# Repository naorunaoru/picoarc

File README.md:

# PicoARC

PicoARC is a device that appears to the host as a USB audio interface and passes through incoming audio as an S/PDIF-style stream to an ARC-compatible device. In simpler terms, this allows you to output audio from your computer to a soundbar or an ARC-capable receiver. It builds as USB Audio Class 1 by default for broad host compatibility; USB Audio Class 2 remains available as an opt-in target.

It also allows you to control the soundbar's volume. Somewhat. Because apparently supporting absolute volume control over CEC is not something that vendors are eager to implement.

Host volume and mute changes propagate to the soundbar in both USB modes. The
latest soundbar state is returned by subsequent USB control queries. UAC2 also
sends AudioControl change notifications; UAC1 has no notification endpoint, so
host volume controls generally remain stale after an on-device adjustment.
Host interfaces may ignore the UAC2 notifications as well.

Did I tell you it does HDMI-CEC too? Yes, it does, because it's required for ARC negotiation.

## Why?

There's no off-the-shelf way of doing this exact thing, surprisingly. The closest thing is using S/PDIF, which has limited bandwidth, sometimes incurs additional latency and definitely does not allow you to control the soundbar from the host.

## How does it work?

On the USB side, it acts as an audio interface, grabs the audio stream and passes it through.

On the HDMI side, it pretends to be a TV: responds to DDC queries with a plausible EDID, negotiates ARC with the connected audio system over CEC and drives the ARC line within the constraints defined by the HDMI 1.4 spec.

## Supported audio formats

- PCM at 32/44.1/48/88.2/96 kHz (higher sample rates are out of the question because RP2040 only has USB Full Speed)
- 16/20/24-bit

The optional UAC2 target additionally exposes separate IEC 61937 Dolby Digital
(AC-3) and DTS passthrough alternates. They are omitted from the default UAC1
target because host-driver support for Type III transport is inconsistent.

## Hardware

The PCB design lives under `hardware/`. The schematic source is written in
[Zener](https://docs.pcb.new/pages/spec), so `hardware/picoarc.zen` is the
schematic/netlist source of truth rather than a `.kicad_sch`; the KiCad layout
and JLCPCB production files are checked in alongside it.

See [hardware/README.md](hardware/README.md) for the hardware file map,
Zener/KiCad workflow, and the old hand-wired Pico prototype wiring.

## License

PicoARC uses a split license. Hardware design materials are licensed under
`CERN-OHL-W-2.0`, and firmware plus general project documentation are licensed
under `MIT`. See [LICENSE](LICENSE) for the exact scope and full license text
locations.

## Build requirements

- Git
- CMake and Ninja
- Arm GNU toolchain
- `picotool`

The Pico SDK and TinyUSB sources are pinned as git submodules under
`firmware/third_party`; builds do not use SDK copies installed on the host.
PicoARC uses Pico SDK 2.2.0 and upstream TinyUSB 0.21.0.

## Build

From this directory:

```sh
git submodule update --init --recursive
make build
```

This configures and builds both firmware variants:

```text
firmware/build-release/picoarc-release.uf2
firmware/build-debug/picoarc-debug.uf2
```

Those are UAC1 builds. To build the opt-in UAC2 target instead:

```sh
make build-uac2
```

Its artifacts use separate build directories and names so CMake and host USB
caches cannot mix the two personalities:

```text
firmware/build-release-uac2/picoarc-release-uac2.uf2
firmware/build-debug-uac2/picoarc-debug-uac2.uf2
```

UAC1 is the recommended full-speed target and is the mode tested for Windows
compatibility. Treat UAC2 as experimental on full-speed hosts; it is retained
for IEC 61937 and uses an adaptive OUT endpoint without explicit feedback. The
firmware follows the host's delivery rate by servoing the S/PDIF PIO clock from
the receive-buffer level.

The equivalent helper option is `--usb-audio-class uac2` (or `--uac uac2`),
for example `./picoarc build release --uac uac2`. Direct CMake builds can set
`-DPICOARC_USB_AUDIO_CLASS=uac2`; omitting the option selects UAC1.

By default PicoARC keeps sending silence for five minutes after the host closes
its audio stream, then stops the ARC/S/PDIF carrier so the soundbar can go to
standby. This can prevent short notification sounds from being swallowed while
the soundbar wakes during gaps between playback. To change the timeout, edit
`firmware/src/picoarc_config.h` before building:

```c
#define PICOARC_IDLE_AUDIO_TIMEOUT_SECONDS 300
```

Use `0` to stop immediately, positive seconds for a timeout, or `-1` to keep
sending silence forever. Reopening the stream cancels the countdown; the next
close starts a fresh countdown. Silent audio within an open stream and temporary
buffer refills do not start it. With a finite timeout, the carrier stays off at
boot until a stream opens; `-1` sends silence from boot.

The release variant is audio-only with logging compiled out. It waits for an
HDMI ARC device, completes ARC/SAD capability discovery, asks the soundbar for
its OSD name, and then enumerates as USB audio using that name when the soundbar
provides one. USB sample rates are limited to the connected soundbar's reported
capabilities. UAC1 lists rates separately for each PCM bit depth; UAC2 reports
the available rates on its shared clock and validates the selected format when
starting a stream. Unsupported bit depths and codecs are omitted. UAC2 rejects
unsupported rate requests; UAC1 rounds them to a supported rate and reports the
selected value through GET_CUR. When SAD discovery is unavailable, the existing
fallback remains 16-bit PCM at 48 kHz.

Capabilities are frozen for each USB connection and refreshed by re-enumerating
when they change. The initial rate is 48 kHz if supported, otherwise the nearest
supported rate. The debug variant initially exposes its serial log and reset
interface with no streaming alternates, then briefly reconnects USB when audio
capabilities become available or change.

## Host sanitizer tests

The host tests require CMake, Ninja, and a native Clang or GCC installation
with AddressSanitizer and UndefinedBehaviorSanitizer runtimes. They do not need
the Pico SDK or Arm compiler, but the TinyUSB submodule must be initialized. Run them with the
default C compiler or select one before the first configure:

```sh
make test-sanitizers
CC=clang make test-sanitizers
```

The compiler selection is cached in `firmware/build-host-sanitizers`; remove
that generated directory before switching compilers. The tests compile the
same USB audio sample decoder used by the firmware and cover the supported
16-, 20-, and 24-bit subslots, including IEC 61937 words, unaligned byte input,
buffer bounds, and the maximum audio-task batch. They also compile the real USB
descriptors and control callbacks for both audio classes and debug layouts,
checking sample-rate negotiation, sink changes, fallback capabilities, and
unsupported format/rate requests.

Run the idle timeout checks for both USB audio classes with a simulated clock:

```sh
python3 firmware/tests/test_idle_audio.py
```

The RP2040 firmware remains on its normal embedded build path and is not
instrumented. Host tests cannot validate DMA and PIO timing, multicore races,
interrupt behavior, or flash-blackout behavior on the device.

## Flash

Connect the Pico over USB, then run:

```sh
make flash
```

The helper script builds the release firmware first, then uses `picotool` to
load and run the UF2. If the Pico is not detected, hold BOOTSEL while plugging
it in and run the command again.

To flash the optional UAC2 release build, use `make flash-uac2`.

## Monitor

To open the USB serial log:

```sh
make monitor
```

To build, flash, and then open the monitor in one step:

```sh
make run
```

This flashes the debug variant, because the release variant does not expose a
USB serial log.

`make run-uac2` does the same with the optional UAC2 debug build.

Press `Ctrl-]` to close the monitor.

## Inspect silent audio

For a connected adapter that stops producing sound while volume controls still
work, an optional release build exposes read-only USB audio diagnostics while
keeping the same audio interfaces and descriptors:

```sh
cmake -S firmware -B firmware/build-diagnostics-uac2 -G Ninja \
  -DPICOARC_VARIANT=release -DPICOARC_USB_AUDIO_CLASS=uac2 \
  -DPICOARC_USB_DIAGNOSTICS=ON
cmake --build firmware/build-diagnostics-uac2
```

Flash `firmware/build-diagnostics-uac2/picoarc-release-uac2-diagnostics.uf2`
using BOOTSEL, then capture during playback or a failure before reconnecting USB:

```sh
python3 tools/audio_probe.py --seconds 30 > audio-diagnostics.jsonl
```

The probe requires libusb and reports audio counters, ARC gating, DMA progress,
output hardware state, and reset cause without clearing counters or claiming
interfaces.
During a bounded capture it waits for the adapter to return after a KVM switch;
an uptime reset means the board rebooted, while `watchdog_timeout` and
`watchdog_forced` distinguish watchdog resets from hardware resets.
Reset-cause flags require diagnostic protocol version 2; output registers,
nonzero encoded-frame counts, and encoder/buffer hashes require version 3,
and unavailable fields are omitted for older firmware.
Growing USB/frame counters with a stopped DMA block counter indicate a stuck
output core; a closed format gate points to ARC/capability state, while growing
DMA blocks with admitted nonzero audio require checking the carrier and receiver.
Diagnostics are disabled by default and provide evidence for debugging rather
than changing recovery behavior.

Protocol 3 diagnostics also provide an explicit software BOOTSEL command;
ordinary captures remain read-only, and rebooting requires the board's USB
serial number:

```sh
python3 tools/audio_probe.py --bootsel --serial YOUR_BOARD_SERIAL
```

Protocol 4 can also copy the encoded 192-frame buffer currently being consumed
by DMA, without pausing playback:

```sh
python3 tools/audio_probe.py --spdif-block --serial YOUR_BOARD_SERIAL
```

The snapshot includes the encoded words, current PIO instruction and pin-pad
configuration. The host decoder checks preambles, BMC transitions, parity and
sample validity, and reports PCM peak/RMS levels and channel-status bytes.
Copies that cross a DMA buffer handoff are marked unstable and must be retried.
This checks the data supplied to PIO; it does not measure the HDMI waveform or
confirm that the soundbar has locked onto it. Ordinary captures omit this larger
snapshot.

Protocol 5 adds two explicit recovery commands, both requiring the matching
USB serial number:

```sh
python3 tools/audio_probe.py --recover output --serial YOUR_BOARD_SERIAL
python3 tools/audio_probe.py --recover usb --serial YOUR_BOARD_SERIAL
```

Capture the failed stream first, then try one recovery at a time. `output`
asks core 1 to restart its S/PDIF state machine and DMA without restarting USB
or ARC negotiation. `usb` reconnects the USB audio device without rebooting the
adapter or reinitializing the S/PDIF state machine. Both briefly interrupt
playback. Read-only captures report output request/completion counters and USB
reconnect requests; an accepted command is not proof that sound has returned.
These commands are diagnostic experiments, not automatic recovery policies.

Protocol 6 adds read-only HPD/DDC controller state and cached soundbar volume
and mute reports, plus an explicit HDMI recovery command:

```sh
python3 tools/audio_probe.py --recover hdmi --serial YOUR_BOARD_SERIAL
```

This reconnects USB, resets the EDID responder and ARC session, and pulses HPD
while retaining processor uptime and the S/PDIF transmitter configuration.
It briefly interrupts playback and reports the request in subsequent captures.
Test it during a captured silent failure to determine whether that boundary
restores sound; an accepted request alone does not establish recovery.

Protocol 8 retains the last 128 observed USB/ARC state changes, streaming-alt
requests, parsed CEC frames and CEC transmit results in memory, with timestamps
and sequence numbers. Capture this history before a reset; reads preserve it,
while a processor restart clears it:

```sh
python3 tools/audio_probe.py --trace --spdif-block --serial YOUR_BOARD_SERIAL
```

The following manual tests separate parts of the combined HDMI recovery:

| Command | Direct action |
| --- | --- |
| `--recover ddc` | Reset only the EDID I2C controller, FIFOs and byte parser |
| `--recover cec-rx` | Reset only the CEC receiver and parser |
| `--recover cec` | Resend the existing system-audio and ARC-initiation requests |
| `--recover hpd` | Pulse HPD low for 200 ms, retaining cached ARC and EDID state |

Each command requires `--serial`; none explicitly reconnects USB or restarts
the audio transmitter, although soundbar replies can trigger normal ARC/USB
state changes. Try one command at a time during a captured silent failure and
check audibility and the trace before proceeding; these diagnostics introduce
no automatic recovery or idle refresh.

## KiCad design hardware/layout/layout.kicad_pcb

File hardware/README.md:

# PicoARC Hardware

The PicoARC PCB design lives in this directory. This branch contains
[completed USB-powered DDC routing](experiments/usb-powered-ddc.md) for using
the board with separate monitor-flashing firmware. Layout checks pass;
electrical bring-up remains outstanding. The circuit is
authored with the [Zener](https://docs.pcb.new/pages/spec) toolchain from
[Diode](https://github.com/diodeinc/pcb), and the physical board layout is kept
as a generated/synced [KiCad](https://kicad.org/) project.

## Source of Truth

Zener is a Starlark-based hardware description language for PCB schematics. The
`pcb` CLI evaluates the `.zen` design, manages dependencies from `pcb.toml`,
assigns reference designators, validates the netlist, and generates/syncs KiCad
layout files.

In this repo, the `.zen` files are the schematic source of truth. There is no
separate `.kicad_sch` to edit:

- `picoarc.zen` is the top-level board schematic/netlist.
- `modules/` contains reusable schematic subcircuits for USB-C, power, HDMI
  ARC, and debug/status hardware.
- `components/` contains local RP2040 and flash component definitions.
- `footprints/` contains local symbols, footprints, and 3D models not taken
  directly from the upstream KiCad libraries.

Edit the Zen module tree when changing the circuit, then regenerate/sync the
KiCad layout from that source.

## Debug Probe Access

`TP_SWD` is a compact row of three 1.0 x 2.0 mm edge test pads on 1.5 mm pitch.
Connect it to Raspberry Pi Debug Probe using pogo pins or soldered leads. Its
target-side pinout is:

- pin 1: SWCLK / SC
- pin 2: GND
- pin 3: SWDIO / SD

The SWCLK and SWDIO pads currently connect directly to the RP2040. Target-side
100 ohm series termination is intentionally omitted while the board layout is
in flux and should be reconsidered before fabrication. The center ground pad
and the board's other solderable ground test pads use thermal-relief zone
connections to make hand soldering practical.

## Layout and Production Files

- `pcb.toml` is the Zener workspace/board manifest. It pins the board entry
  point, repository metadata, `pcb-version`, and KiCad library dependencies.
- `layout/layout.kicad_pro` is the KiCad project to open for board review.
- `layout/layout.kicad_pcb` is the checked-in PCB layout.
- `layout/layout.kicad_dru` contains KiCad design rules.
- `layout/jlcpcb/gerber/` contains the plotted Gerber/drill outputs.
- `layout/jlcpcb/production_files/` contains the current JLCPCB upload bundle:
  `GERBER-layout.zip`, `BOM-layout.csv`, and `CPL-layout.csv`.
- `jlcpcb-lcsc.csv` records JLCPCB/LCSC sourcing data used by the board.

## Zener/KiCad Workflow

Install the `pcb` shim using the
[upstream instructions](https://docs.pcb.new/pages/quickstart). The shim selects
the `pcbc` toolchain lane requested by `pcb.toml`; this repo currently requests
the `0.3` lane.

After changing the Zen schematic, run from this directory:

```sh
pcb sync
pcb build picoarc.zen
pcb layout picoarc.zen
```

`pcb sync` reconciles imports and dependency manifests. `pcb build` evaluates
and validates the Zener design. `pcb layout` regenerates/syncs the KiCad layout
project from the Zen netlist.

After that, open `layout/layout.kicad_pro` in KiCad for placement/routing
review, DRC, and fabrication exports. KiCad remains the tool for inspecting and
finishing the physical layout; Zener remains the tool for changing the circuit.

## Prototype Wiring

If you want to reproduce the old hand-wired Pico dev-board prototype instead,
the minimal wiring is:

- Pi Pico dev board
- HDMI breakout
- Few passives you probably have laying around
- 3.3 V <-> 5 V I2C level shifter for HDMI DDC/EDID (or not, if you're brave)

```text
Net CEC_BUS
  Pico 3V3 (pin 36)  -- R1 (27 kOhm) -- node CEC_BUS
  Pico GP3 (pin 5)   -- R2 (220 Ohm) -- node CEC_BUS
  node CEC_BUS                         -- HDMI pin 13

Net ARC_TX
  Pico GP2 (pin 4)   -- R3 (330 Ohm) -- node ATT_A
  node ATT_A         -- R4 (56 Ohm)  -- Pico GND
  node ATT_A         -- C1 (10 nF)   -- HDMI pin 14

Net HDMI_5V_FROM_SOUNDBAR
  HDMI pin 18        -- R5 (1 kOhm)   -- HDMI pin 19
  HDMI pin 18        -- R6 (68 kOhm)  -- node HDMI_5V_SENSE
  node HDMI_5V_SENSE                   -- Pico GP4 (pin 6)
  node HDMI_5V_SENSE -- R7 (100 kOhm) -- Pico GND

Net DDC_EDID
  HDMI pin 15 (SCL)  -- level shifter -- Pico GP7 (pin 10)
  HDMI pin 16 (SDA)  -- level shifter -- Pico GP6 (pin 9)

Net GND
  Pico GND (pin 38)                    -- HDMI pin 17
```

Note about DDC_EDID: while omitting a level shifter works as a bench-only direct
GPIO bodge, keep in mind that HDMI DDC is a 5 V bus and RP2040 IO is not exactly
5 V tolerant.

## License

The PicoARC hardware design materials in this directory are licensed under the
CERN Open Hardware Licence Version 2 - Weakly Reciprocal (`CERN-OHL-W-2.0`).
See [../LICENSE](../LICENSE) for the repository license notice and full license
text locations.

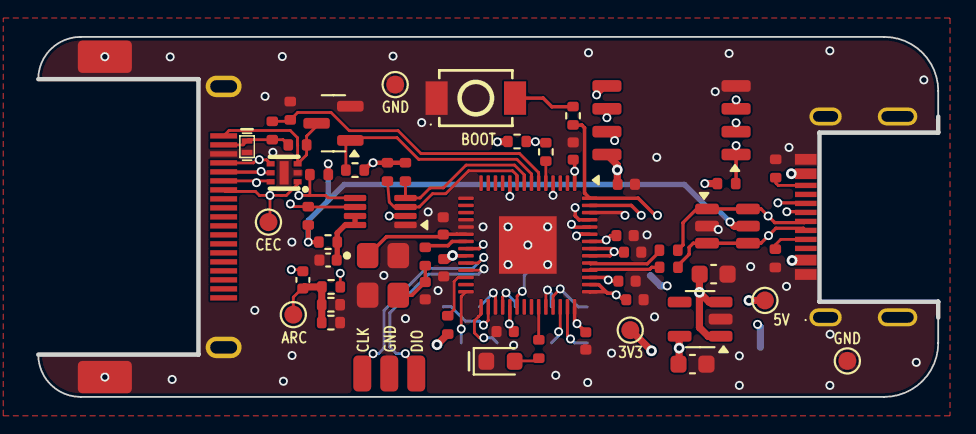
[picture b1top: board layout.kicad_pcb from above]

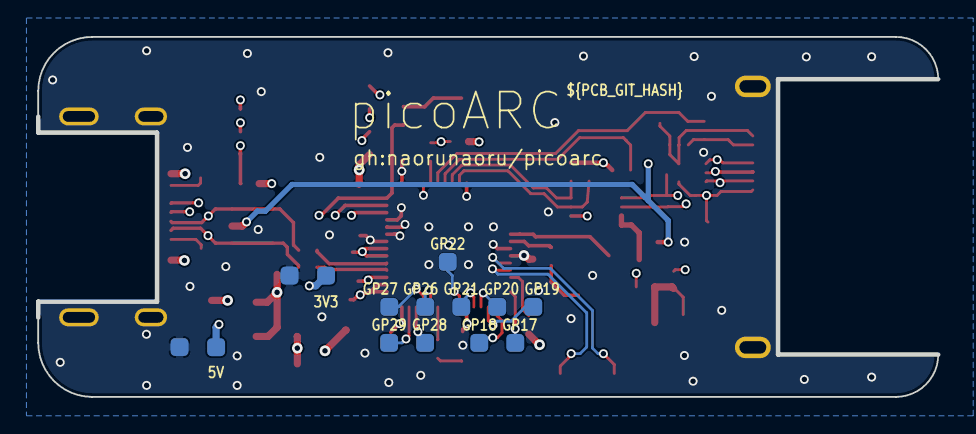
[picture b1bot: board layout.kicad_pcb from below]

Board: 4 copper layers, 50.0 x 19.8 mm, 72 parts (14 on the bottom side), 49 nets.

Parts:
C1: CL05B103KB5NNNC; C_0402_1005Metric
C2: 0402CG101J500NT; C_0402_1005Metric
C3, C4: CL10A106MA8NRNC; C_0603_1608Metric
C5, C8, C9, C10, C11, C12, C13: CL05B104KB54PNC; C_0402_1005Metric
C6, C7: CL05A105KA5NQNC; C_0402_1005Metric
C14, C15: 0402CG330J500NT; C_0402_1005Metric
D1: KT-0603R; LED_0603_1608Metric
D2: D5V0M5B6LP16-7; DFN1616-6_L1.6-W1.6-P0.50-BL-EP
D3: H7VH10U; SOD-882_L1.0-W0.6-BI
J1: HC-HDMI0019T-3; HDMI-SMD_HC-HDMI0019T-3_PicoARC_R6
J2: GT-USB-7014G; USB-C-SMD_GT-USB-7014D
Q1: 2N7002; SOT-23
R1: 0402WGF2202TCE; R_0402_1005Metric
R2: 0402WGF2200TCE; R_0402_1005Metric
R3: 0402WGF3300TCE; R_0402_1005Metric
R4, R5, R16, R23: 0402WGF1001TCE; R_0402_1005Metric
R6, R7, R13: 0402WGF1003TCE; R_0402_1005Metric
R8, R9, R10, R11: 0402WGF2201TCE; R_0402_1005Metric
R12: 0402WGF2003TCE; R_0402_1005Metric
R14: 0402WGF1000TCE; R_0402_1005Metric
R15: 0402WGF1200TCE; R_0402_1005Metric
R17, R18: 0402WGF5101TCE; R_0402_1005Metric
R19, R20: 0402WGF1002TCE; R_0402_1005Metric
R21, R22: 0402WGF330JTCE; R_0402_1005Metric
SW1: TS-1088-AR02016; SW-SMD_L3.9-W3.0-P4.45
TP1, TP2, TP3, TP4, TP5, TP6, TP7, TP8, TP9, TP10, TP11, TP12, TP13, TP14: ?; TestPad_1.0x1.0mm_RoundRect
TP15: ?; SWD_EdgePads_1x03_P1.50mm
TP16, TP17, TP18, TP19, TP20, TP21: ?; TestPoint_Pad_D1.0mm
U1: PCA9306DCUR; VSSOP-8_2.3x2mm_P0.5mm
U2: AP2112K-3.3TRG1; SOT-23-5
U3: USBLC6-2SC6; SOT-23-6
U4: W25Q16JVSSIQ; SOIC-8_5.3x5.3mm_P1.27mm
U5: RP2040; QFN-56-1EP_7x7mm_P0.4mm_EP3.2x3.2mm
Y1: X322512MSB4SI; Crystal_SMD_3225-4Pin_3.2x2.5mm

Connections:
ARC_TX: R3.1, U5.4
ATT_A: C1.1, R3.2, R14.1, R15.1, TP18.1
BOOTSEL_SW: R16.2, SW1.1
CEC_BUS: R2.1, U5.5
CEC_NODE: D2.1, J1.13, R1.2, R2.2, TP19.1
DBG.STATUS_LED_A: D1.2, R4.2
DDC_SCL: R8.1, U1.3, U5.9
DDC_SCL_5V: D2.5, J1.15, R10.1, U1.6
DDC_SDA: R9.1, U1.4, U5.8
DDC_SDA_5V: D2.4, J1.16, R11.1, U1.5
GND: C2.2, C3.2, C4.2, C5.2, C6.2, C7.2, C8.2, C9.2, C10.2, C11.2, C12.2, C13.2, C14.2, C15.2, D1.1, D2.2, D2.7, D3.2, J1.17, J1.SH, J2.A1, J2.A12, J2.B1, J2.B12, J2.S1, Q1.2, R7.2, R14.2, R15.2, R17.2, R18.2, SW1.2, TP3.1, TP4.1, TP15.2, TP20.1, TP21.1, U1.1, U2.2, U3.2, U4.4, U5.19, U5.57, Y1.2, Y1.4
GP17: TP5.1, U5.28
GP18: TP6.1, U5.29
GP19: TP7.1, U5.30
GP20: TP8.1, U5.31
GP21: TP9.1, U5.32
GP22: TP10.1, U5.34
GP26: TP11.1, U5.38
GP27: TP12.1, U5.39
GP28: TP13.1, U5.40
GP29: TP14.1, U5.41
HDMI._ARC14: C1.2, D2.6, J1.14
HDMI._HDMI_5V: D3.1, J1.18, R5.1, R6.1
HDMI._HPD: D2.3, J1.19, Q1.3, R5.2
HDMI._VREF2_EN: C2.1, R12.2, U1.7, U1.8
HDMI_5V_SENSE: R6.2, R7.1, U5.6
HPD_GATE: Q1.1, R13.1, U5.7
QSPI_CLK: U4.6, U5.52
QSPI_CS: R16.1, R19.1, U4.1, U5.56
QSPI_IO0: U4.5, U5.53
QSPI_IO1: U4.2, U5.55
QSPI_IO2: U4.3, U5.54
QSPI_IO3: U4.7, U5.51
RUN: R20.1, U5.26
STATUS_LED: R4.1, U5.37
SWD_SWCLK: TP15.1, U5.24
SWD_SWDIO: TP15.3, U5.25
USBC.CC1: J2.A5, R17.1
USBC.CC2: J2.B5, R18.1
USB_D_N: J2.A7, J2.B7, R21.2, U3.3, U3.4
USB_D_P: J2.A6, J2.B6, R22.2, U3.1, U3.6
U_MCU.RP_USB_D_N: R21.1, U5.46
U_MCU.RP_USB_D_P: R22.1, U5.47
U_MCU._R_OSC: C15.1, R23.1, Y1.3
U_MCU.oscpair_XIN: C14.1, U5.20, Y1.1
U_MCU.oscpair_XOUT: R23.2, U5.21
VDD_1V1: C6.1, C8.1, C9.1, U5.23, U5.45, U5.50
VDD_3V3: C4.1, C5.1, C7.1, C10.1, C11.1, C12.1, C13.1, R1.1, R8.2, R9.2, R13.2, R19.2, R20.2, TP1.1, TP16.1, U1.2, U2.5, U4.8, U5.1, U5.10, U5.22, U5.33, U5.42, U5.43, U5.44, U5.48, U5.49
VDD_5V: C3.1, J2.A4, J2.A9, J2.B4, J2.B9, R10.2, R11.2, R12.1, TP2.1, TP17.1, U2.1, U2.3, U3.5

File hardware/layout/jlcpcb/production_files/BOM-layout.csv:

Comment,Designator,Footprint,LCSC,Quantity
D5V0M5B6LP16-7,D2,DFN1616-6_L1.6-W1.6-P0.50-BL-EP,C445551,1
H7VH10U,D3,SOD-882_L1.0-W0.6-BI,C7420372,1
TS-1088-AR02016,SW1,SW-SMD_L3.9-W3.0-P4.45,C720477,1
0402WGF3300TCE,R3,R_0402_1005Metric,,1
0402WGF1001TCE,R5,R_0402_1005Metric,,1
RP2040,U5,QFN-56-1EP_7x7mm_P0.4mm_EP3.2x3.2mm,,1
0402WGF1200TCE,R15,R_0402_1005Metric,,1
0402WGF2202TCE,R1,R_0402_1005Metric,,1
CL05B104KB54PNC,C13,C_0402_1005Metric,,1
0402WGF2201TCE,R10,R_0402_1005Metric,,1
0402WGF1001TCE,R16,R_0402_1005Metric,,1
CL05B104KB54PNC,C8,C_0402_1005Metric,,1
CL05A105KA5NQNC,C7,C_0402_1005Metric,,1
0402WGF1003TCE,R6,R_0402_1005Metric,,1
CL05B104KB54PNC,C9,C_0402_1005Metric,,1
CL05B104KB54PNC,C11,C_0402_1005Metric,,1
0402WGF1002TCE,R20,R_0402_1005Metric,,1
0402WGF1000TCE,R14,R_0402_1005Metric,,1
0402WGF1001TCE,R23,R_0402_1005Metric,,1
CL05B104KB54PNC,C12,C_0402_1005Metric,,1
0402WGF2201TCE,R9,R_0402_1005Metric,,1
0402CG330J500NT,C15,C_0402_1005Metric,,1
0402CG101J500NT,C2,C_0402_1005Metric,,1
0402CG330J500NT,C14,C_0402_1005Metric,,1
CL05B104KB54PNC,C5,C_0402_1005Metric,,1
CL05B104KB54PNC,C10,C_0402_1005Metric,,1
0402WGF1003TCE,R7,R_0402_1005Metric,,1
0402WGF1002TCE,R19,R_0402_1005Metric,,1
0402WGF1001TCE,R4,R_0402_1005Metric,,1
CL10A106MA8NRNC,C3,C_0603_1608Metric,,1
CL05A105KA5NQNC,C6,C_0402_1005Metric,,1
CL05B103KB5NNNC,C1,C_0402_1005Metric,,1
AP2112K-3.3TRG1,U2,SOT-23-5,,1
CL10A106MA8NRNC,C4,C_0603_1608Metric,,1
2N7002,Q1,SOT-23,,1
208658-1001,J1,HDMI_A_Molex_208658-1001_Horizontal,,1
0402WGF5101TCE,R18,R_0402_1005Metric,,1
USBLC6-2SC6,U3,SOT-23-6,,1
X322512MSB4SI,Y1,Crystal_SMD_3225-4Pin_3.2x2.5mm,,1
0402WGF2200TCE,R2,R_0402_1005Metric,,1
W25Q16JVSSIQ,U4,SOIC-8_5.3x5.3mm_P1.27mm,,1
0402WGF330JTCE,R22,R_0402_1005Metric,,1
0402WGF2003TCE,R12,R_0402_1005Metric,,1
USB4105-GF-A-060,J2,USB_C_Receptacle_GCT_USB4105-xx-A_16P_TopMnt_Horizontal,,1
0402WGF1003TCE,R13,R_0402_1005Metric,,1
0402WGF2201TCE,R11,R_0402_1005Metric,,1
0402WGF2201TCE,R8,R_0402_1005Metric,,1
0402WGF5101TCE,R17,R_0402_1005Metric,,1
KT-0603R,D1,LED_0603_1608Metric,,1
PCA9306DCTR,U1,VSSOP-8_2.3x2mm_P0.5mm,,1
0402WGF330JTCE,R21,R_0402_1005Metric,,1

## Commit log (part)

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2026-05-18 initial firmware, works as 16bit 48khz sink
2026-05-18 feat: CEC in PIO
2026-05-19 fix: rm player persona experiments
2026-05-19 feat(cec): TX via PIO+DMA with yield-aware wait
    Move CEC transmission and the per-byte ACK slot onto a single PIO
    state machine fed by DMA. The SM runs at 1 MHz so every loop
    iteration is exactly 1 us; per-action dispatch overhead is
    constant for the chained command order the encoder produces, so
    on-the-wire timing is independent of DMA timing.
    ACK sampling now happens inside the PIO at 1050 us after the
2026-05-19 feat(usb-audio): add 48k/24-bit streaming alt
    UAC2 streaming interface now exposes alt 1 (48 kHz / 16-bit PCM,
    the original v1 format) and alt 2 (48 kHz / 24-bit packed PCM,
    3-byte samples) alongside the mandatory alt 0. The host picks at
    SET_INTERFACE time; the audio task parses 2- or 3-byte
    little-endian samples accordingly and feeds spdif a single
    24-bit-left-aligned int32 representation either way.
2026-05-19 feat(arc): bidirectional CEC volume/mute sync
    Host-side feature unit (mute + volume RW) drives soundbar volume
    over CEC, and unsolicited <Report Audio Status> from the soundbar
    drives the host's reported volume back via tud_audio_int_write
    on the AC interrupt EP.
    Outbound flow tries absolute volume first with
    <Set Audio Volume Level> (CEC 2.0 opcode 0x73). If the soundbar
2026-05-19 fix(audio): init spdif before USB starts handling control transfers
    macOS issues SET CUR on the clock source during enumeration to
    restore the last-selected sample rate, well before main()
    reached spdif_start. The audio callback ran with spdif_pio
    still NULL, so pio_sm_set_clkdiv wrote to NULL + 0xC8 (in flash)
    instead of PIO0.SM0.CLKDIV — silently failing while still
    returning success from the control transfer. The device then
2026-05-19 Treat GP4 as HDMI 5V sense
2026-05-19 Add IEC 61937 DD/DTS passthrough
2026-05-20 Clean repo layout and gate audio by ARC capabilities
    Add repo-local ignores and helper targets, stop tracking generated firmware build outputs, and keep a placeholder for future hardware files.
    Expand USB audio descriptors/rates, gate streaming against ARC SAD support, and query/log CEC audio capability details.
2026-05-20 add README.md at last
2026-05-20 Update README
    Added information about HDMI-CEC support.
2026-05-20 chore: more reasonable state machine
2026-05-20 feat: move CEC back to PIO, add CEC series resistor
2026-05-20 fix: report volume change back
2026-05-20 fix: ci build
2026-05-20 fix: ci build (again)
2026-05-21 Make idle ARC carrier configurable
    Add a firmware config header for the idle audio keepalive policy, support an off S/PDIF mode when idle, and stop the idle CEC probe loop once ARC is ready.
2026-05-21 Update status LED indications
2026-05-25 Add DDC EDID responder for ARC bring-up
2026-05-25 Document DDC EDID wiring
2026-05-29 hardware: scaffold pcb board workspace
2026-05-29 hardware: add diodeinc/kicad + stdlib dependencies
    Adds github.com/diodeinc/kicad@0.2.2 as a direct dependency so that
    RP2040 and other KiCad reference modules resolve via the @kicad/... import
    prefix. Also adds hardware/.gitignore to exclude pcb tool cache artifacts.
2026-05-29 hardware: add configured RP2040 reference module
    Instantiates the @kicad/MCU_RaspberryPi/RP2040.zen reference module as
    U_MCU with firmware-matching GPIO assignments (ARC_TX/CEC_BUS/HDMI_5V_SENSE
    on gpio2-4, DDC_SDA/SCL on gpio6-7, STATUS_LED on gpio25), crystal, BOOTSEL
    button, and SWD test points; 23 components total.
2026-05-29 hardware: add Power module (AP2112K-3.3, bus-powered)
2026-05-29 hardware: add USB-C module with CC Rd and USBLC6 ESD
2026-05-29 hardware: add HDMI ARC/CEC/DDC front-end (PCA9306 + 5V ESD array)
2026-05-29 hardware: add status LED on GP25
2026-05-29 hardware: add bring-up test points (power, ARC+CEC, DDC)
2026-05-29 hardware: add 5V-sense divider electrical check
2026-05-29 hardware: generate initial KiCad layout (60 footprints, unrouted)
2026-05-29 hardware: add MPNs to authored components (clears 6/9 BOM errors, enables per-module schematic view)
2026-05-29 hardware: set repository name; drop unused kicad vendor glob
2026-05-31 hardware: DRC relaxation pass — 4-layer planes, pours, net classes, cost rules, clean silk
    Checkpoint of the bring-up layout before the RP2040-module refactor.
    - Planes/pours: In1=GND plane, In2=VDD_3V3 plane, F/B GND pours, GND
    stitch-via grid + QFN exposed-pad thermal vias.
    - Resolved real DRC: track/pad clearances (incl. QSPI_IO3<->C7 via a
    small C7 nudge), dangling vias/tracks, starved thermals
    (min_resolved_spokes 2->1), isolated copper.
2026-05-31 docs: design spec — custom RP2040 module + all-Basic BOM re-spec
    Approved design for owning the RP2040 support circuit (clone-and-trim of the
    vendored module), pinning all passives to JLCPCB Basic parts, dropping the unused
    GPIO header/breakouts, and adding bidirectional ARC/HDMI-5V ESD. Checkpoint before
    implementation.
2026-05-31 docs: implementation plan — custom RP2040 module + all-Basic BOM
    Milestone plan with a critical post-re-sync layout-preservation gate (revert to
    6ed3f1d if the layout is wiped) and high-value-first sequencing (J2/SW1 footprint swaps
    isolated last so a footprint-sourcing snag can't block the core all-Basic + ESD work).
2026-05-31 docs: resolved JLCPCB Basic parts reference (RP2040 refactor)
    Verified Basic MPNs/LCSC# for the all-Basic re-spec, plus the value-subs and the
    ESD/LDO/switch resolutions. Companion to the implementation plan.
2026-05-31 hardware: keep small Omron B3U-1000P for SW1 (no small JLC-Basic tact exists)
    Only JLC-Basic SMD tact is the 5.1x5.1mm TS-1187A; all small ones (B3U 3x2.5mm,
    EVQ 3.6x3.5mm) are Extended. For a rarely-pressed BOOTSEL button the ~$3 feeder fee
    beats sacrificing ~5x5mm of board, so revert SW1 to the original small B3U. Also means
    SW1's footprint now matches the placed layout (one fewer part to reconcile).
2026-05-31 hardware: SW1 -> TS-1088-AR02016 (4x3mm JLC-Basic tact) via easyeda2kicad footprint
    The 4x3mm TS-1088 is the small JLC-Basic SMD tact (C720477, free). No KiCad lib
    footprint exists, so generated one with easyeda2kicad (--lcsc_id=C720477) and added
    it locally at footprints/picoarc.pretty/. Uses the generic Switch:SW_Push symbol
    (2 pads, 1/2) + the local footprint; stripped the broken /tmp 3D-model ref. pcb build
    clean (59 components). SW1 now Basic -> Extended floor back to ~8.
2026-05-31 hardware: add SW1 (TS-1088) 3D model + portable ${KIPRJMOD} model path
2026-06-12 hardware: shrink to 50x22mm, backside GPIO pads, DRC/netclass cleanup
    - board outline 50.0x22.0mm: fits JLCPCB's cheap <=50x50 4-layer tier
    - 14 backside expansion pads (1x1mm roundrect): GP17-22, GP26-29 (all
    4 ADC), 3V3/5V/GND; net-name silk labels instead of TP designators
    - netclasses: drop *USB_D_* shadow pattern (pair now routes true 90R
    0.1867/0.127), RP_USB_D_* stubs into 90Ohm Diff, 50Ohm SE 0.2mm
    - kicad_dru: retarget fine-pitch pad rule U2->U1 (refdes shuffle),
2026-06-13 hardware: pre-production fixes (PCA9306 bias, HPD gate FET, BOOTSEL 1k, 33pF xtal caps)
    Schematic review findings, all new parts JLC-Basic:
    - PCA9306: EN+VREF2 shorted and biased from cable 5V via R12 200k + C2 100pF
    per TI SCPS113O (was: VREF2 hard-tied to 5V, EN to 3V3 - pass-FET damage
    risk and below the VREF1+0.6V enable minimum)
    - HPD: Q1 2N7002 holds HPD low (gate pulled to 3V3 by R13 100k) until
    firmware drives new GP5/HPD_GATE low once the EDID slave is ready;
2026-06-13 fix: reroute ATT_A in a less roundabout way
2026-06-13 fix: no more vias in pads, @ivanlevsky should be proud
2026-06-13 fix: I like to move it move it
2026-06-13 chore: move docs/superpowers out of repo to ../docs/picoarc
2026-06-13 fix: angular USB diff pair go!
2026-06-14 hardware: QSPI reroute, board shrink, things moved here and there
2026-06-24 feat(fab): LCSC overlay parsing + seed map
2026-06-24 feat(fab): BOM builder with grouping + LCSC join
2026-06-24 feat(fab): CPL remap + filter to placed designators
2026-06-24 feat(fab): kicad-cli/git/version resolution helpers
2026-06-24 feat(fab): orchestration, CLI, DRC gate + integration test
    Adds main() with --skip-drc/--gerbers-only/--no-zip flags, run/run_drc/
    summarize_drc/export_gerbers/export_drill/export_pos/run_pcb_bom/write_csv/
    zip_dir helpers, and __main__ guard. IntegrationSmokeTest exercises the
    full pipeline against the real board (skip-drc mode); 21/21 tests pass.
2026-06-24 test(fab): close file handles in integration test (pristine output)
2026-06-24 fix(fab): run pcb bom from hardware/ so make fab works from repo root
2026-06-24 fix(fab): test summarize_drc, clean tool-failure errors, doc grouping + make target
2026-06-24 hardware: add backside silkscreen
2026-06-24 fix(fab): group BOM by MPN identity + real footprints so distinct parts don't merge
    build_bom grouped by (value,package,lcsc); pcb bom leaves those blank for ICs/
    connectors, so D2/Q1/SW1 (different parts) collapsed into one row and every IC
    shipped a blank Comment+Footprint. Group by MPN (the orderable identity) instead,
    fall back Comment->MPN and Footprint->pos Package column. Export pos once and reuse
    for BOM + CPL.
2026-06-24 feat(fab): fill LCSC overlay map for passives/LED/MOSFET/crystal/switch
    Web-sourced from LCSC (2026-06-24, needs ordering confirmation). 22 MPNs mapped;
    make fab now warns on only D2 (PESD5V0L4UF 4-ch ESD), which LCSC/JLCPCB does not
    stock — substitute or supply externally.
2026-06-24 hardware: replace HDMI 5V TVS
2026-06-24 feat(fab): JLCPCB CPL rotation correction layer
    remap_cpl passed KiCad rotations through verbatim; KiCad's footprint 0-deg
    orientation disagrees with JLCPCB's part library for SOT-23/VSSOP/SOIC/QFN, so
    parts (U1/U2/U3...) rendered rotated in JLC's preview. Add a footprint-regex +
    per-designator correction table (hardware/jlcpcb-rotations.csv, community-standard
    seeds) applied at CPL generation; connectors/easyeda footprints left uncorrected
    pending preview verification.
2026-06-25 hardware/layout: fix sub-spec vias, add orientation silk, D3 cathode
    Resolve JLCPCB order 12939101A_Y2 + assembly-orientation cleanup:
    - 3 stitching vias were 0.2mm drill / 0.4mm pad (0.1mm annular), which JLC
    flagged for a mandatory paid 4-wire Kelvin test. Resized to the standard
    0.3mm/0.5mm stitching via and refilled all zones (the larger pad needs
    the GND/VDD planes to pull back, or DRC throws clearance errors).
    - Added F.SilkS orientation indicators to the polarized 2-pin parts whose
2026-06-25 hardware: replace D3 +5V TVS with unidirectional H7VH10U
    Swap the cable +5V TVS from H7VN10B (bidirectional, C20615788) to H7VH10U
    (R+O, unidirectional, C51898355). A unidirectional TVS is the correct
    topology for a DC rail, and it's cheaper. Same R+O DFN1006-2L/SOD-882
    package -> drop-in footprint, no layout re-sync needed.
    VRWM 7V / breakdown 7.5V / clamp 15V clears the <=5.3V rail with margin;
    500nA leakage is negligible for the R6/R7 100k sense divider, and the 15V
2026-06-25 hardware: enforce JLCPCB via limits in DRC
    Add two custom rules to layout.kicad_dru so the `make fab` strict-DRC gate
    catches sub-spec vias before ordering (the issue JLC flagged on order
    12939101A_Y2):
    - JLCPCB_min_via_diameter: via diameter >= 0.45mm (JLC process minimum)
    - JLCPCB_small_via_annular_no_kelvin: annular ring >= 0.125mm for holes
    <= 0.2mm, i.e. >= 0.45mm pad on a 0.2mm drill -- below this JLC forces a
